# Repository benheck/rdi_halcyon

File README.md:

# rdi_halcyon
Audio mixer board for the RDI Halcyon prototype game console

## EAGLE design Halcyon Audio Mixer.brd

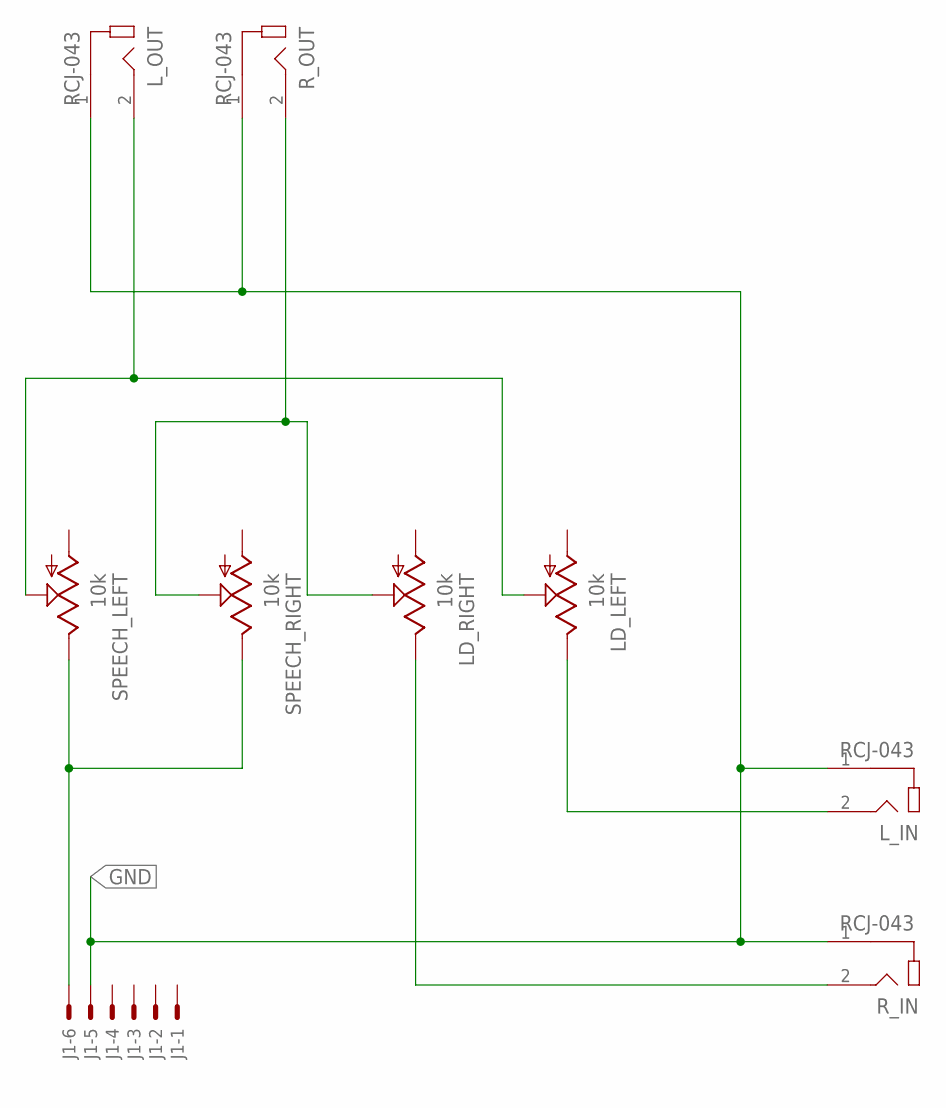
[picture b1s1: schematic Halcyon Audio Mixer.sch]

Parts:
J1: 22-23-2061
LD_LEFT: 10k; B25P
LD_RIGHT: 10k; B25P
L_IN: RCJ-043; CUI_RCJ-043
L_OUT: RCJ-043; CUI_RCJ-043
R_IN: RCJ-043; CUI_RCJ-043
R_OUT: RCJ-043; CUI_RCJ-043
SPEECH_LEFT: 10k; B25P
SPEECH_RIGHT: 10k; B25P

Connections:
GND: J1.5, L_IN.1, L_OUT.1, R_IN.1, R_OUT.1
unnamed: LD_LEFT.E, L_IN.2
unnamed: LD_RIGHT.E, R_IN.2
unnamed: LD_LEFT.S, L_OUT.2, SPEECH_LEFT.S
unnamed: J1.6, SPEECH_LEFT.E, SPEECH_RIGHT.E
unnamed: LD_RIGHT.S, R_OUT.2, SPEECH_RIGHT.S

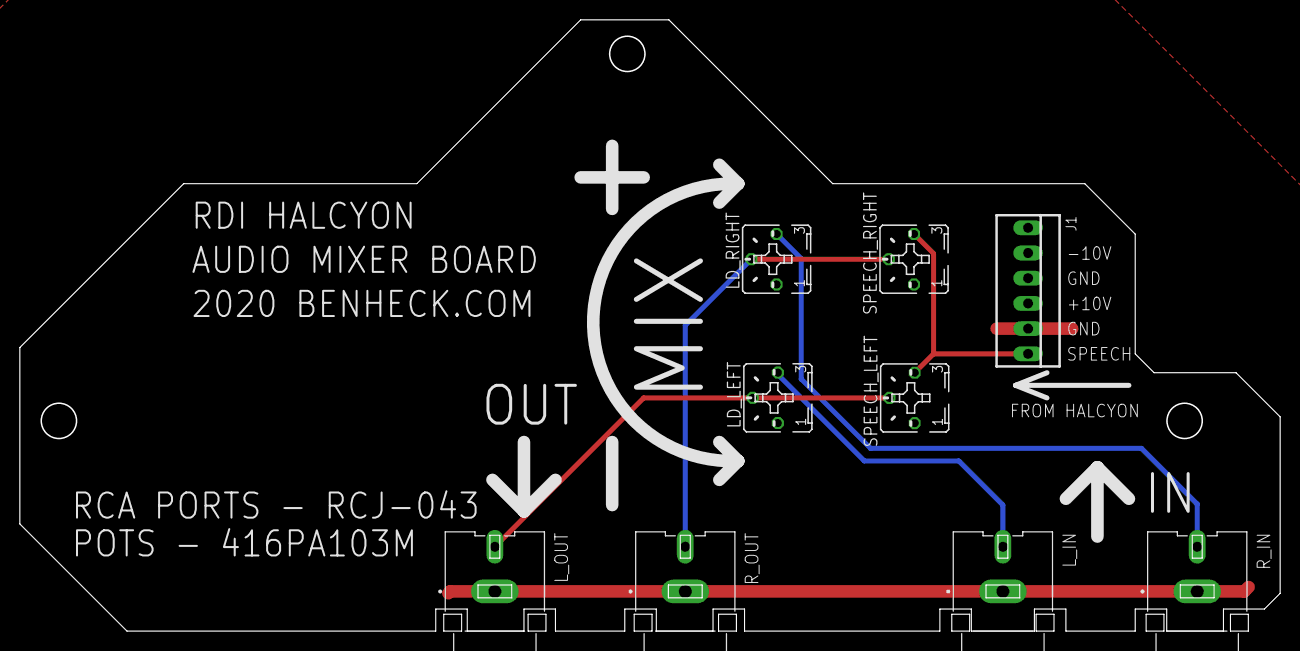
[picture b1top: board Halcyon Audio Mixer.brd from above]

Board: 2 copper layers, 126.8 x 61.4 mm, 9 parts (0 on the bottom side), 6 nets.

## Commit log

2020-11-08 Added files
